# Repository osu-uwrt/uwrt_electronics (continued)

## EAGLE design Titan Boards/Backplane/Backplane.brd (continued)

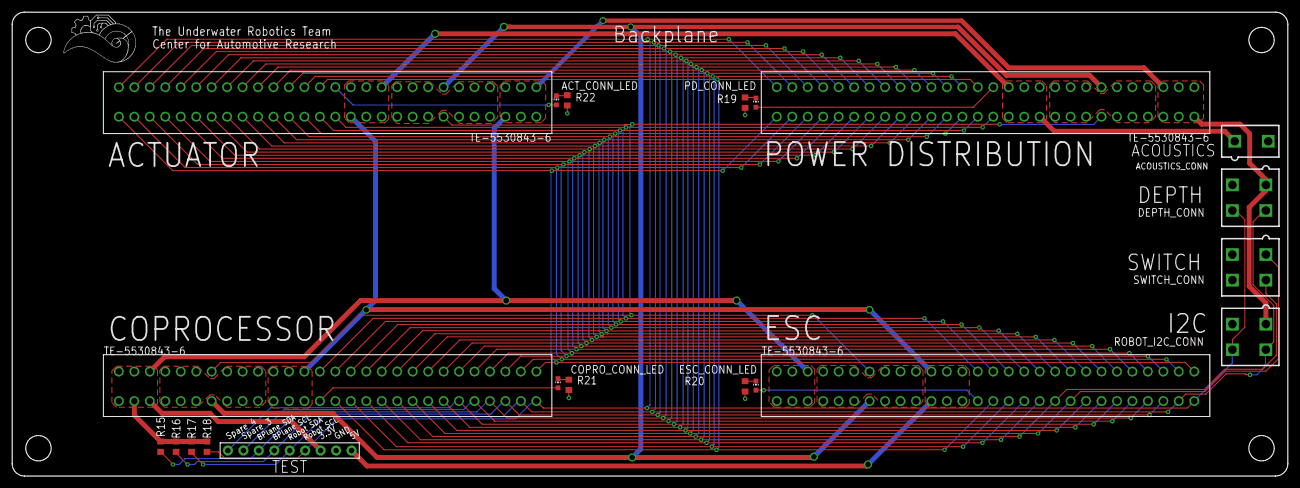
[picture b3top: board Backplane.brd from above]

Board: 2 copper layers, 209.6 x 76.2 mm, 21 parts (0 on the bottom side), 42 nets.

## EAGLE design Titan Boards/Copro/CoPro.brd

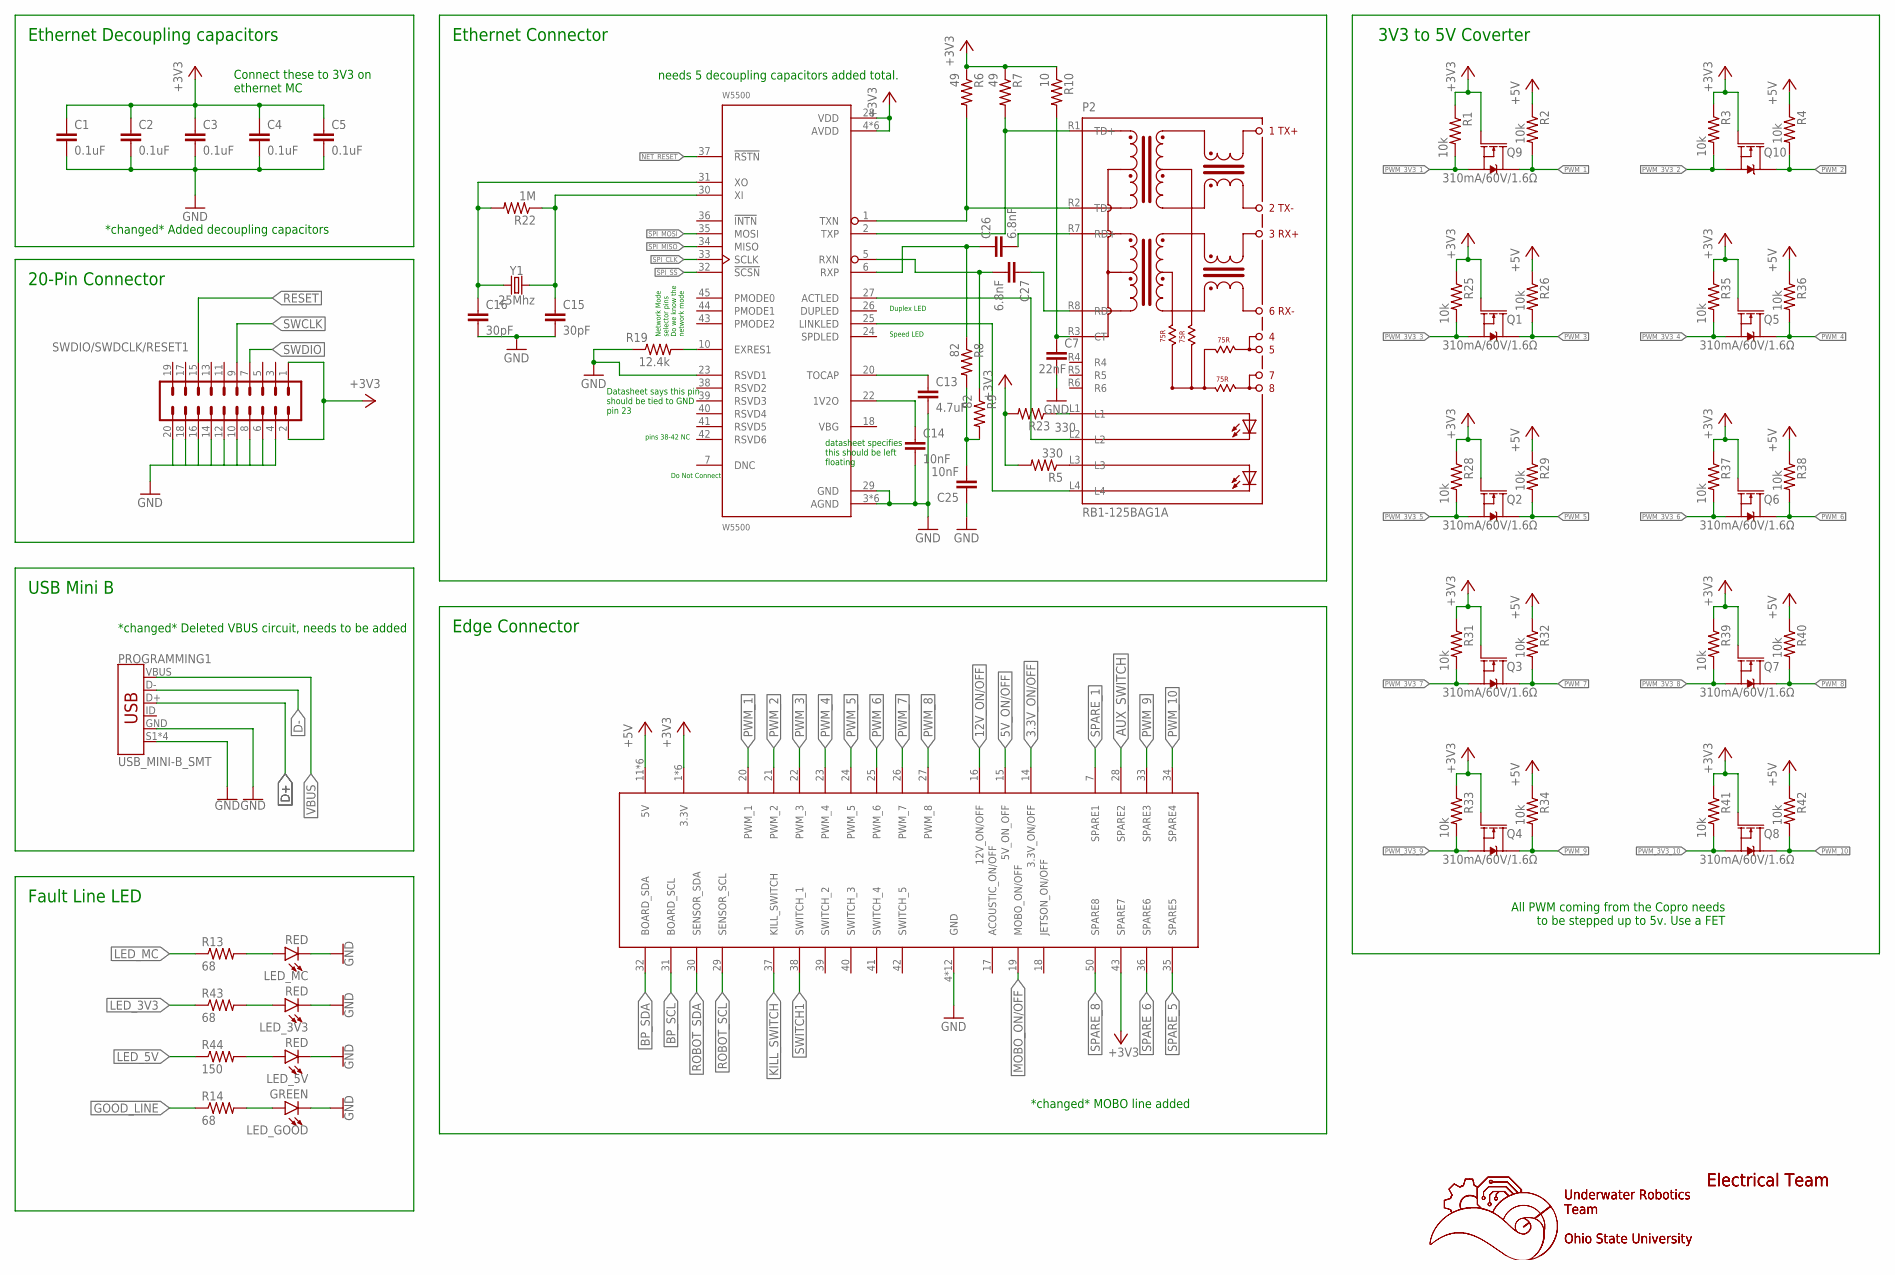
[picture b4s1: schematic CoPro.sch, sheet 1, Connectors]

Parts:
C1, C2, C3, C4, C5: 0.1uF; C0603
C7: 22nF; C0603
C13: 4.7uF; C0603
C14, C25: 10nF; C0603
C15, C16: 30pF; C0603
C26, C27: 6.8nF; C0603
LED_3V3, LED_5V: RED; LED-0603
LED_GOOD: GREEN; LED-0603
LED_MC: RED; LED-0603
P2: RB1-125BAG1A; WIZNET_RB1-125BAG1A
PROGRAMMING1: USB_MINI-B_SMT; USB-MINIB
Q1, Q2, Q3, Q4, Q5, Q6, Q7, Q8, Q9, Q10: 310mA/60V/1.6Ω; SOT323
R1, R2, R3, R4, R25, R26, R28, R29, R31, R32, R33, R34, R35, R36, R37, R38, R39, R40, R41, R42: 10k; R0603
R5, R23: 330; R0603
R6, R7: 49; R0603
R8, R9: 82; R0603
R10: 10; R0603
R13, R14, R43: 68; R0603
R19: 12.4k; R0603
R22: 1M; R0603
R44: 150; R0603
SWDIO/SWDCLK/RESET1: CONN_10X2; 2X10
U$1: 5530843-EDGE; 5530843-6-BOARDFINGERS
W5500: W5500; QFP50P900X900X160-48N
Y1: 25Mhz; HC49US

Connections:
3.3V_ON/OFF: U$1.14 (3.3V_ON/OFF); also elsewhere on the board
5V_ON/OFF: U$1.15 (5V_ON_OFF); also elsewhere on the board
12V_ON/OFF: U$1.16 (12V_ON/OFF); also elsewhere on the board
+3V3: C1.1, C2.1, C3.1, C4.1, C5.1, Q1.1 (G), Q2.1 (G), Q3.1 (G), Q4.1 (G), Q5.1 (G), Q6.1 (G), Q7.1 (G), Q8.1 (G), Q9.1 (G), Q10.1 (G), R1.1, R3.1, R5.2, R6.1, R7.1, R10.1, R23.2, R25.1, R28.1, R31.1, R33.1, R35.1, R37.1, R39.1, R41.1, SWDIO/SWDCLK/RESET1.1, SWDIO/SWDCLK/RESET1.2, U$1.1 (3.3V), U$1.2 (3.3V), U$1.3 (3.3V), U$1.43 (SPARE7), U$1.54 (3.3V), U$1.55 (3.3V), U$1.56 (3.3V), W5500.4 (AVDD), W5500.8 (AVDD), W5500.11 (AVDD), W5500.15 (AVDD), W5500.17 (AVDD), W5500.21 (AVDD), W5500.28 (VDD); also elsewhere on the board
+5V: R2.1, R4.1, R26.1, R29.1, R32.1, R34.1, R36.1, R38.1, R40.1, R42.1, U$1.11 (5V), U$1.12 (5V), U$1.13 (5V), U$1.44 (5V), U$1.45 (5V), U$1.46 (5V); also elsewhere on the board
AUX_SWITCH: U$1.28 (SPARE2)
BP_SCL: U$1.31 (BOARD_SCL); also elsewhere on the board
BP_SDA: U$1.32 (BOARD_SDA); also elsewhere on the board
D+: PROGRAMMING1.D+; also elsewhere on the board
D-: PROGRAMMING1.D-; also elsewhere on the board
GND: C1.2, C2.2, C3.2, C4.2, C5.2, C7.2, C13.2, C14.2, C15.2, C16.2, C25.1, LED_3V3.C, LED_5V.C, LED_GOOD.C, LED_MC.C, PROGRAMMING1.GND, PROGRAMMING1.S1 (SHIELD), PROGRAMMING1.S2 (SHIELD), PROGRAMMING1.S3 (SHIELD), PROGRAMMING1.S4 (SHIELD), R19.1, SWDIO/SWDCLK/RESET1.4, SWDIO/SWDCLK/RESET1.6, SWDIO/SWDCLK/RESET1.8, SWDIO/SWDCLK/RESET1.10, SWDIO/SWDCLK/RESET1.12, SWDIO/SWDCLK/RESET1.14, SWDIO/SWDCLK/RESET1.16, SWDIO/SWDCLK/RESET1.18, SWDIO/SWDCLK/RESET1.20, U$1.4 (GND), U$1.5 (GND), U$1.6 (GND), U$1.8 (GND), U$1.9 (GND), U$1.10 (GND), U$1.47 (GND), U$1.48 (GND), U$1.49 (GND), U$1.51 (GND), U$1.52 (GND), U$1.53 (GND), W5500.3 (AGND), W5500.9 (AGND), W5500.14 (AGND), W5500.16 (AGND), W5500.19 (AGND), W5500.23 (RSVD1), W5500.29 (GND), W5500.48 (AGND); also elsewhere on the board
GOOD_LINE: R14.1; also elsewhere on the board
KILL_SWITCH: U$1.37 (KILL_SWITCH); also elsewhere on the board
LED_3V3: R43.1; also elsewhere on the board
LED_5V: R44.1; also elsewhere on the board
LED_MC: R13.1; also elsewhere on the board
MOBO_ON/OFF: U$1.19 (MOBO_ON/OFF); also elsewhere on the board
unnamed: C14.1, W5500.22 (1V2O)
unnamed: LED_MC.A, R13.2
unnamed: C15.1, R22.1, W5500.30 (XI), Y1.2
unnamed: C16.1, R22.2, W5500.31 (XO), Y1.1
unnamed: P2.L4, W5500.25 (LINKLED)
unnamed: P2.L2, W5500.27 (ACTLED)
unnamed: C13.1, W5500.20 (TOCAP)
unnamed: R19.2, W5500.10 (EXRES1)
unnamed: P2.L1, R23.1
unnamed: P2.L3, R5.1
unnamed: C25.2, R8.2, R9.2
unnamed: P2.R1 (TD+), R7.2, W5500.2 (TXP)
unnamed: P2.R2 (TD-), R6.2, W5500.1 (TXN)
unnamed: C26.2, P2.R7 (RD+)
unnamed: C26.1, R8.1, W5500.6 (RXP)
unnamed: C27.2, R9.1, W5500.5 (RXN)
unnamed: C27.1, P2.R8 (RD-)
unnamed: C7.1, P2.R3 (CT), R10.2
unnamed: LED_3V3.A, R43.2
unnamed: LED_5V.A, R44.2
unnamed: LED_GOOD.A, R14.2
NET_RESET: W5500.37 (!RSTN); also elsewhere on the board
PWM_1: Q9.3 (D), R2.2, U$1.20 (PWM_1)
PWM_2: Q10.3 (D), R4.2, U$1.21 (PWM_2)
PWM_3: Q1.3 (D), R26.2, U$1.22 (PWM_3)
PWM_3V3_1: Q9.2 (S), R1.2; also elsewhere on the board
PWM_3V3_2: Q10.2 (S), R3.2; also elsewhere on the board
PWM_3V3_3: Q1.2 (S), R25.2; also elsewhere on the board
PWM_3V3_4: Q5.2 (S), R35.2; also elsewhere on the board
PWM_3V3_5: Q2.2 (S), R28.2; also elsewhere on the board
PWM_3V3_6: Q6.2 (S), R37.2; also elsewhere on the board
PWM_3V3_7: Q3.2 (S), R31.2; also elsewhere on the board
PWM_3V3_8: Q7.2 (S), R39.2; also elsewhere on the board
PWM_3V3_9: Q4.2 (S), R33.2; also elsewhere on the board
PWM_3V3_10: Q8.2 (S), R41.2; also elsewhere on the board
PWM_4: Q5.3 (D), R36.2, U$1.23 (PWM_4)
PWM_5: Q2.3 (D), R29.2, U$1.24 (PWM_5)
PWM_6: Q6.3 (D), R38.2, U$1.25 (PWM_6)
PWM_7: Q3.3 (D), R32.2, U$1.26 (PWM_7)
PWM_8: Q7.3 (D), R40.2, U$1.27 (PWM_8)
PWM_9: Q4.3 (D), R34.2, U$1.33 (SPARE3)
PWM_10: Q8.3 (D), R42.2, U$1.34 (SPARE4)
RESET: SWDIO/SWDCLK/RESET1.15; also elsewhere on the board
ROBOT_SCL: U$1.29 (SENSOR_SCL); also elsewhere on the board
ROBOT_SDA: U$1.30 (SENSOR_SDA); also elsewhere on the board
SPARE_1: U$1.7 (SPARE1); also elsewhere on the board
SPARE_5: U$1.35 (SPARE5); also elsewhere on the board
SPARE_6: U$1.36 (SPARE6); also elsewhere on the board
SPARE_8: U$1.50 (SPARE8); also elsewhere on the board
SPI_CLK: W5500.33 (SCLK); also elsewhere on the board
SPI_MISO: W5500.34 (MISO); also elsewhere on the board
SPI_MOSI: W5500.35 (MOSI); also elsewhere on the board
SPI_SS: W5500.32 (!SCSN); also elsewhere on the board
SWCLK: SWDIO/SWDCLK/RESET1.9; also elsewhere on the board
SWDIO: SWDIO/SWDCLK/RESET1.7; also elsewhere on the board
SWITCH1: U$1.38 (SWITCH_1); also elsewhere on the board
VBUS: PROGRAMMING1.VBUS; also elsewhere on the board

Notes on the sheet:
Underwater Robotics Team Ohio State University
Electrical Team
All PWM coming from the Copro needs to be stepped up to 5v. Use a FET
3V3 to 5V Coverter
datasheet specifies this should be left floating
Datasheet says this pin should be tied to GND pin 23
pins 38-42 NC
Do Not Connect
Duplex LED
Speed LED
Network Mode selector pins Do we know the network mode
Ethernet Connector
Edge Connector
20-Pin Connector
Fault Line LED
USB Mini B
needs 5 decoupling capacitors added total.
Ethernet Decoupling capacitors
Connect these to 3V3 on ethernet MC
*changed* Deleted VBUS circuit, needs to be added
*changed* Added decoupling capacitors
*changed* MOBO line added

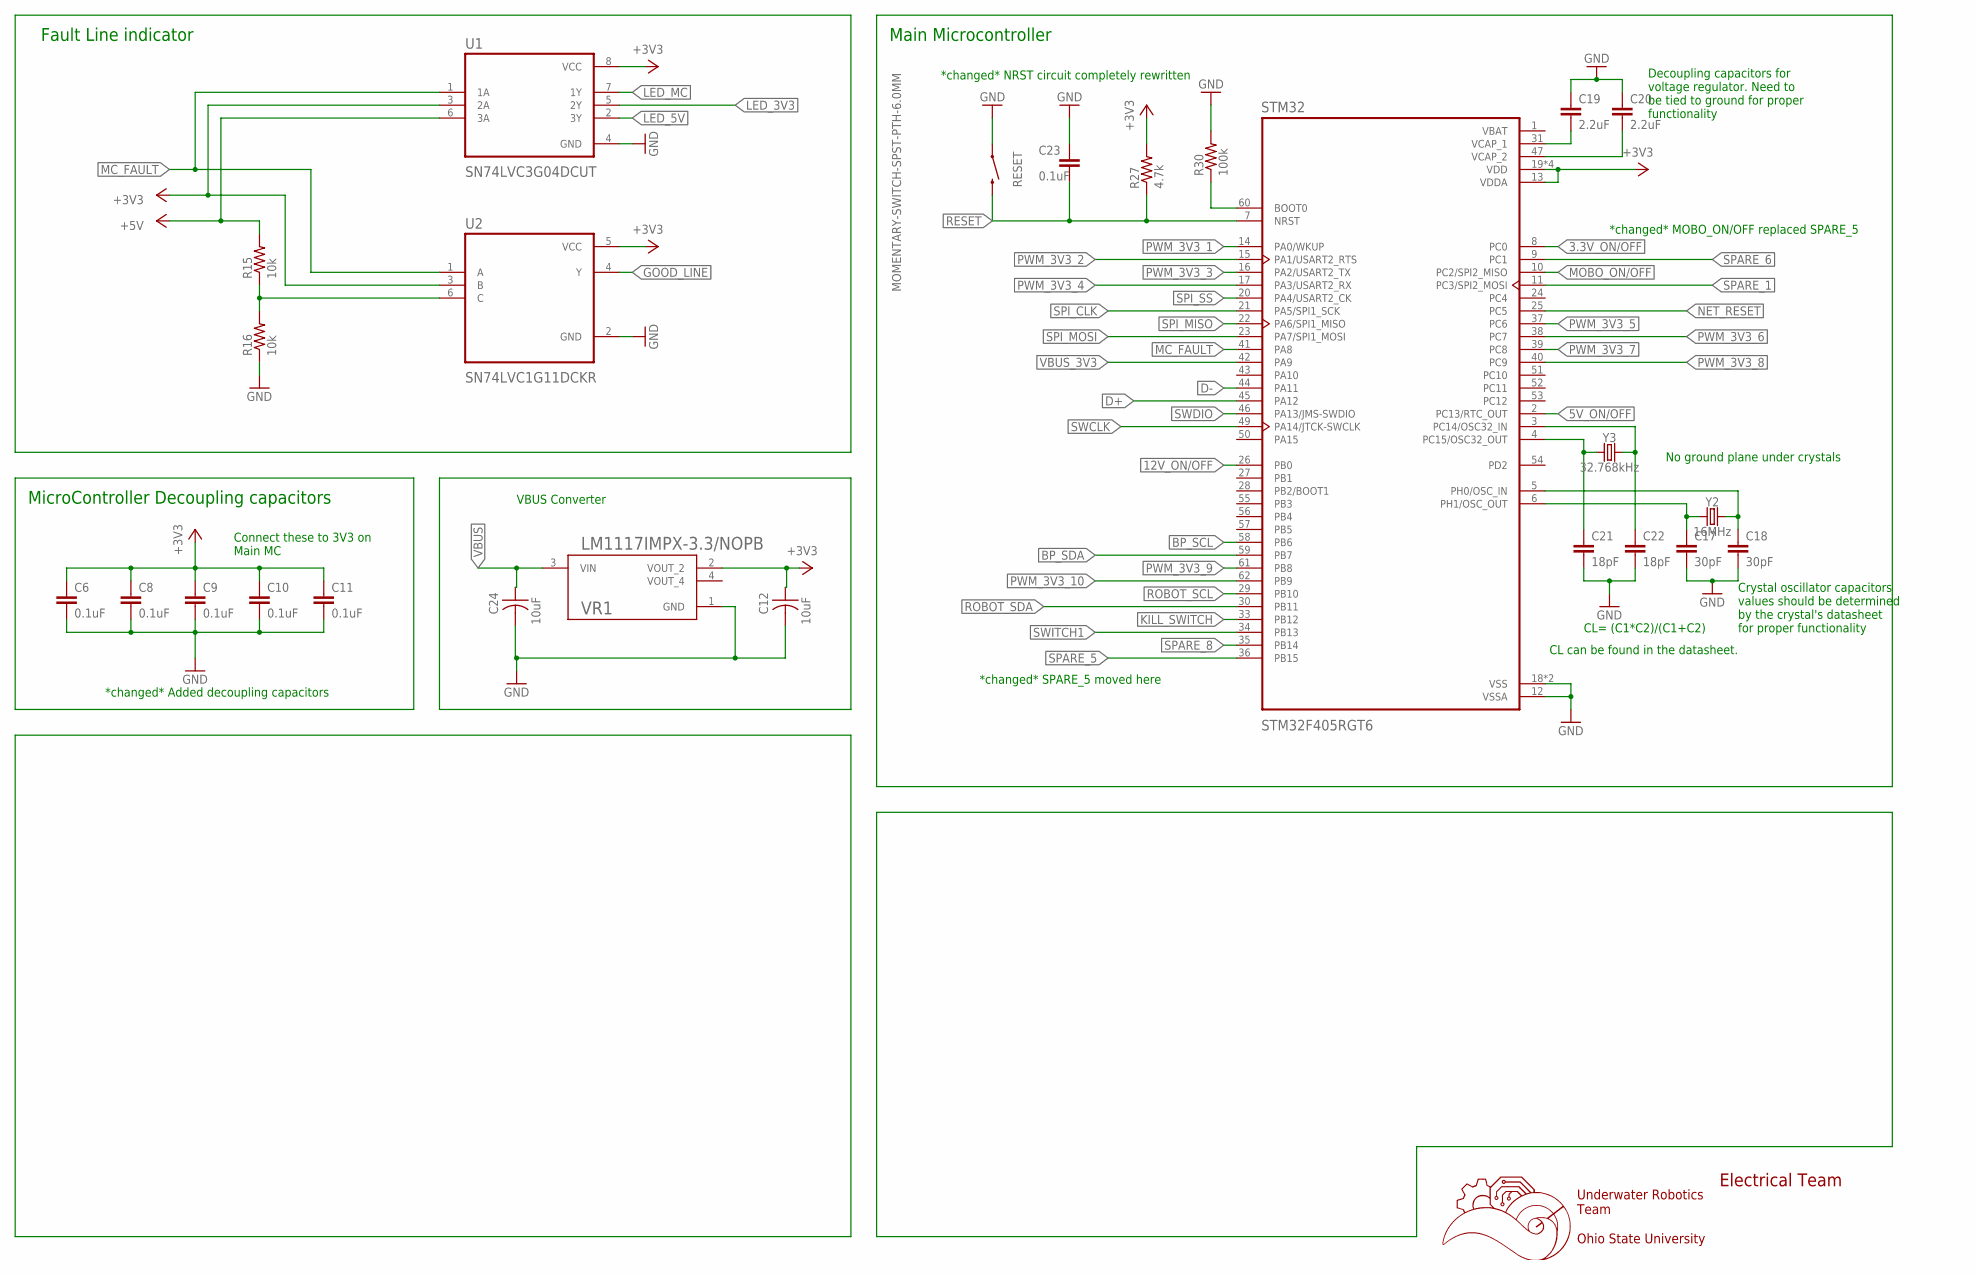
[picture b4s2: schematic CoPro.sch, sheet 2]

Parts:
C6, C8, C9, C10, C11, C23: 0.1uF; C0603
C12, C24: 10uF; C0603
C17, C18: 30pF; C0603
C19, C20: 2.2uF; C0603
C21, C22: 18pF; C0603
R15, R16: 10k; R0603
R27: 4.7k; R0603
R30: 100k; R0603
RESET: MOMENTARY-SWITCH-SPST-PTH-6.0MM; TACTILE_SWITCH_PTH_6.0MM
STM32: STM32F405RGT6; QFP50P1200X1200X160-64N
U1: SN74LVC3G04DCUT; SOP50P310X90-8N
U2: SN74LVC1G11DCKR; SOT65P210X110-6N
VR1: LM1117IMPX-3.3/NOPB; VREG_LM1117IMPX-3.3/NOPB
Y2: 16MHz; HC49US
Y3: 32.768kHz; CRYSTAL-SMD-3.2X1.5MM

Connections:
3.3V_ON/OFF: STM32.8 (PC0); also elsewhere on the board
5V_ON/OFF: STM32.2 (PC13/RTC_OUT); also elsewhere on the board
12V_ON/OFF: STM32.26 (PB0); also elsewhere on the board
+3V3: C6.1, C8.1, C9.1, C10.1, C11.1, C12.1, R27.2, STM32.13 (VDDA), STM32.19 (VDD), STM32.32 (VDD), STM32.48 (VDD), STM32.64 (VDD), U1.3 (2A), U1.8 (VCC), U2.3 (B), U2.5 (VCC), VR1.2 (VOUT_2); also elsewhere on the board
+5V: R15.2, U1.6 (3A); also elsewhere on the board
BP_SCL: STM32.58 (PB6); also elsewhere on the board
BP_SDA: STM32.59 (PB7); also elsewhere on the board
D+: STM32.45 (PA12); also elsewhere on the board
D-: STM32.44 (PA11); also elsewhere on the board
GND: C6.2, C8.2, C9.2, C10.2, C11.2, C12.2, C17.2, C18.2, C19.1, C20.1, C21.2, C22.2, C23.1, C24.2, R16.1, R30.2, RESET.1, STM32.12 (VSSA), STM32.18 (VSS), STM32.63 (VSS), U1.4 (GND), U2.2 (GND), VR1.1 (GND); also elsewhere on the board
GOOD_LINE: U2.4 (Y); also elsewhere on the board
KILL_SWITCH: STM32.33 (PB12); also elsewhere on the board
LED_3V3: U1.5 (2Y); also elsewhere on the board
LED_5V: U1.2 (3Y); also elsewhere on the board
LED_MC: U1.7 (1Y); also elsewhere on the board
MC_FAULT: STM32.41 (PA8), U1.1 (1A), U2.1 (A)
MOBO_ON/OFF: STM32.10 (PC2/SPI2_MISO); also elsewhere on the board
unnamed: C17.1, STM32.6 (PH1/OSC_OUT), Y2.1
unnamed: C18.1, STM32.5 (PH0/OSC_IN), Y2.2
unnamed: C20.2, STM32.47 (VCAP_2)
unnamed: C19.2, STM32.31 (VCAP_1)
unnamed: C21.1, STM32.4 (PC15/OSC32_OUT), Y3.P$1 (1)
unnamed: C22.1, STM32.3 (PC14/OSC32_IN), Y3.P$2 (2)
unnamed: R30.1, STM32.60 (BOOT0)
unnamed: R15.1, R16.2, U2.6 (C)
NET_RESET: STM32.25 (PC5); also elsewhere on the board
PWM_3V3_1: STM32.14 (PA0/WKUP); also elsewhere on the board
PWM_3V3_2: STM32.15 (PA1/USART2_RTS); also elsewhere on the board
PWM_3V3_3: STM32.16 (PA2/USART2_TX); also elsewhere on the board
PWM_3V3_4: STM32.17 (PA3/USART2_RX); also elsewhere on the board
PWM_3V3_5: STM32.37 (PC6); also elsewhere on the board
PWM_3V3_6: STM32.38 (PC7); also elsewhere on the board
PWM_3V3_7: STM32.39 (PC8); also elsewhere on the board
PWM_3V3_8: STM32.40 (PC9); also elsewhere on the board
PWM_3V3_9: STM32.61 (PB8); also elsewhere on the board
PWM_3V3_10: STM32.62 (PB9); also elsewhere on the board
RESET: C23.2, R27.1, RESET.3 (2), STM32.7 (NRST); also elsewhere on the board
ROBOT_SCL: STM32.29 (PB10); also elsewhere on the board
ROBOT_SDA: STM32.30 (PB11); also elsewhere on the board
SPARE_1: STM32.11 (PC3/SPI2_MOSI); also elsewhere on the board
SPARE_5: STM32.36 (PB15); also elsewhere on the board
SPARE_6: STM32.9 (PC1); also elsewhere on the board
SPARE_8: STM32.35 (PB14); also elsewhere on the board
SPI_CLK: STM32.21 (PA5/SPI1_SCK); also elsewhere on the board
SPI_MISO: STM32.22 (PA6/SPI1_MISO); also elsewhere on the board
SPI_MOSI: STM32.23 (PA7/SPI1_MOSI); also elsewhere on the board
SPI_SS: STM32.20 (PA4/USART2_CK); also elsewhere on the board
SWCLK: STM32.49 (PA14/JTCK-SWCLK); also elsewhere on the board
SWDIO: STM32.46 (PA13/JMS-SWDIO); also elsewhere on the board
SWITCH1: STM32.34 (PB13); also elsewhere on the board
VBAT: STM32.1 (VBAT)
VBUS: C24.1, VR1.3 (VIN); also elsewhere on the board
VBUS_3V3: STM32.42 (PA9)

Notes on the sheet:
Underwater Robotics Team Ohio State University
Electrical Team
Decoupling capacitors for voltage regulator. Need to be tied to ground for proper functionality
Crystal oscillator capacitors values should be determined by the crystal's datasheet for proper functionality
CL= (C1*C2)/(C1+C2)
CL can be found in the datasheet.
No ground plane under crystals
Main Microcontroller
Fault Line indicator
*changed* MOBO_ON/OFF replaced SPARE_5
*changed* SPARE_5 moved here
*changed* NRST circuit completely rewritten
MicroController Decoupling capacitors
Connect these to 3V3 on Main MC
*changed* Added decoupling capacitors
VBUS Converter

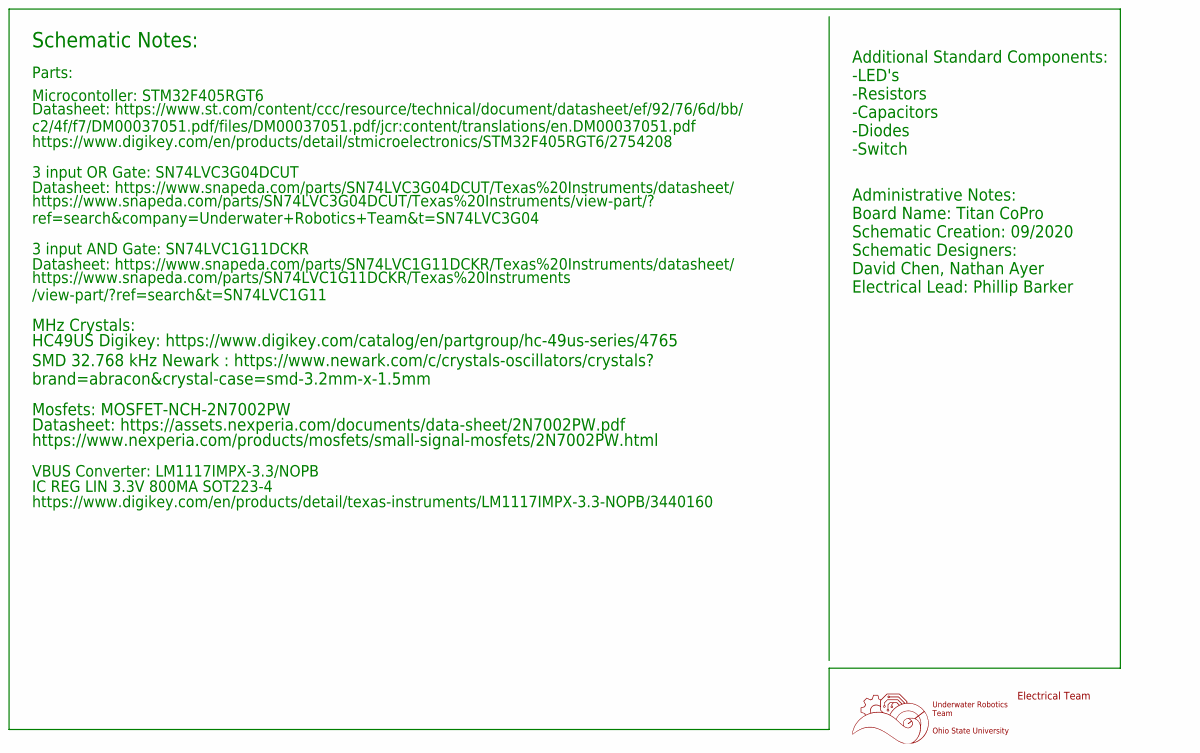
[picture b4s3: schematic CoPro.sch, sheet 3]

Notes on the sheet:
Underwater Robotics Team Ohio State University
Electrical Team
Schematic Notes:
Parts:
Microcontoller: STM32F405RGT6
Datasheet: https://www.st.com/content/ccc/resource/technical/document/datasheet/ef/92/76/6d/bb/ c2/4f/f7/DM00037051.pdf/files/DM00037051.pdf/jcr:content/translations/en.DM00037051.pdf
https://www.digikey.com/en/products/detail/stmicroelectronics/STM32F405RGT6/2754208
3 input OR Gate: SN74LVC3G04DCUT
Datasheet: https://www.snapeda.com/parts/SN74LVC3G04DCUT/Texas%20Instruments/datasheet/
https://www.snapeda.com/parts/SN74LVC3G04DCUT/Texas%20Instruments/view-part/? ref=search&company=Underwater+Robotics+Team&t=SN74LVC3G04
3 input AND Gate: SN74LVC1G11DCKR
Datasheet: https://www.snapeda.com/parts/SN74LVC1G11DCKR/Texas%20Instruments/datasheet/
https://www.snapeda.com/parts/SN74LVC1G11DCKR/Texas%20Instruments /view-part/?ref=search&t=SN74LVC1G11
Additional Standard Components: -LED's -Resistors -Capacitors -Diodes -Switch
Administrative Notes: Board Name: Titan CoPro Schematic Creation: 09/2020 Schematic Designers: David Chen, Nathan Ayer Electrical Lead: Phillip Barker
MHz Crystals:
HC49US Digikey: https://www.digikey.com/catalog/en/partgroup/hc-49us-series/4765
SMD 32.768 kHz Newark : https://www.newark.com/c/crystals-oscillators/crystals? brand=abracon&crystal-case=smd-3.2mm-x-1.5mm
Mosfets: MOSFET-NCH-2N7002PW
Datasheet: https://assets.nexperia.com/documents/data-sheet/2N7002PW.pdf
https://www.nexperia.com/products/mosfets/small-signal-mosfets/2N7002PW.html
VBUS Converter: LM1117IMPX-3.3/NOPB
IC REG LIN 3.3V 800MA SOT223-4
https://www.digikey.com/en/products/detail/texas-instruments/LM1117IMPX-3.3-NOPB/3440160

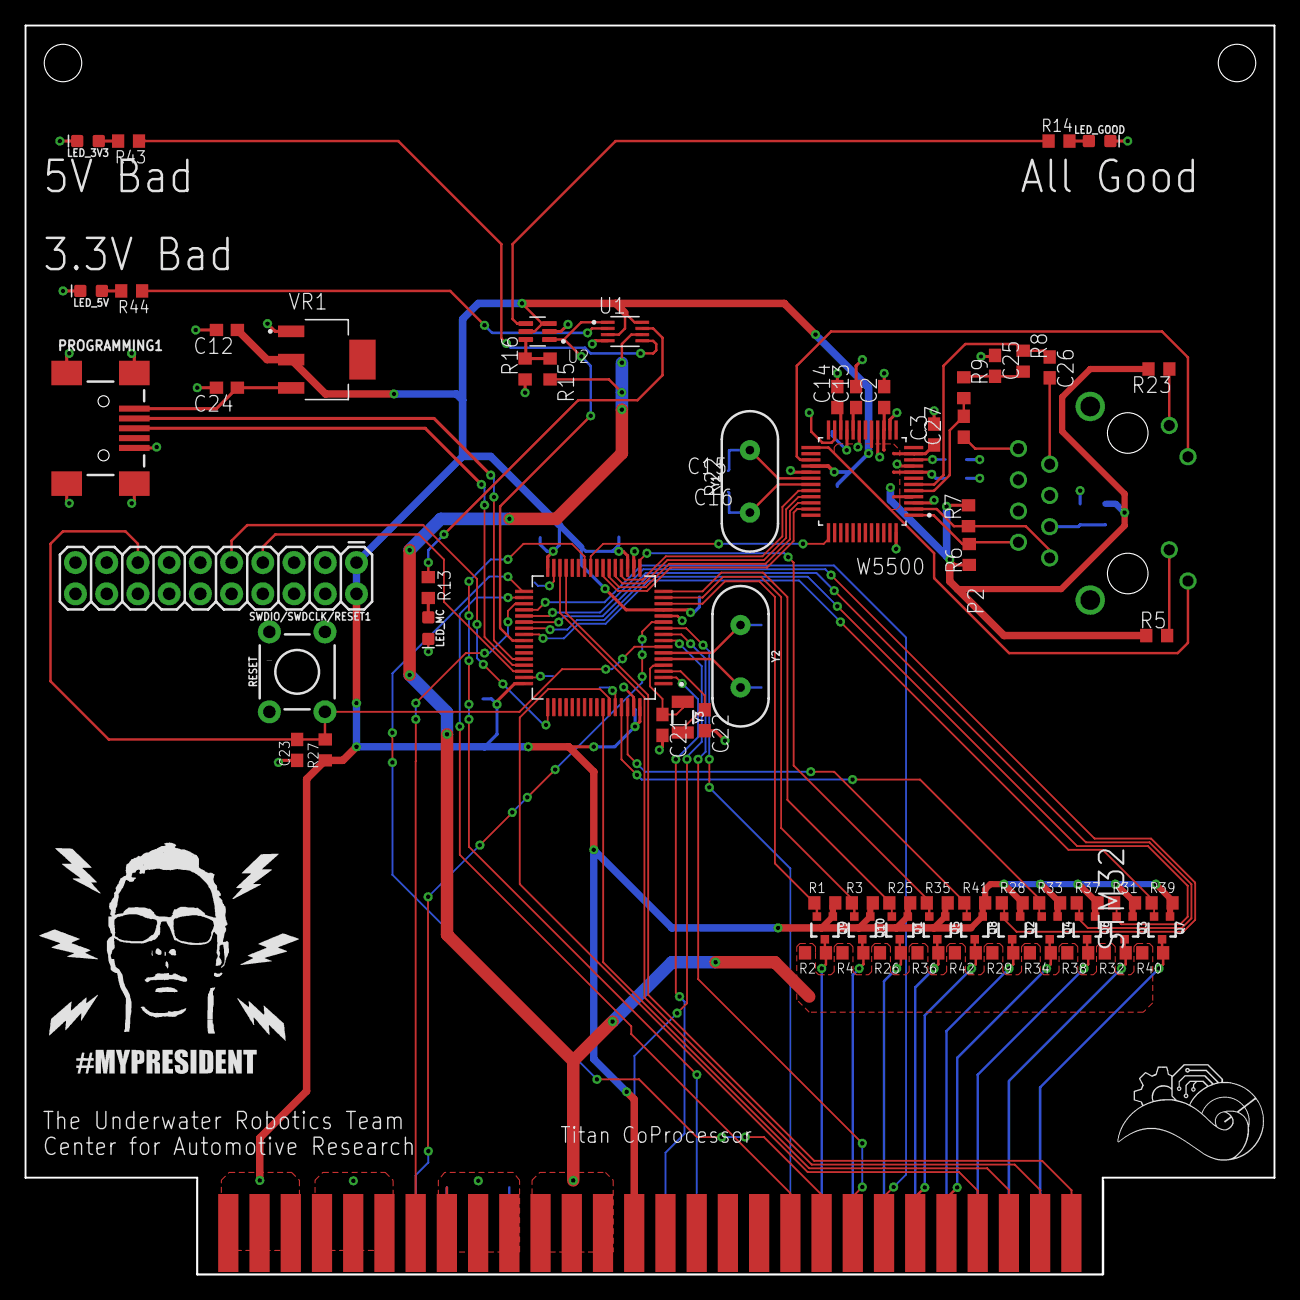
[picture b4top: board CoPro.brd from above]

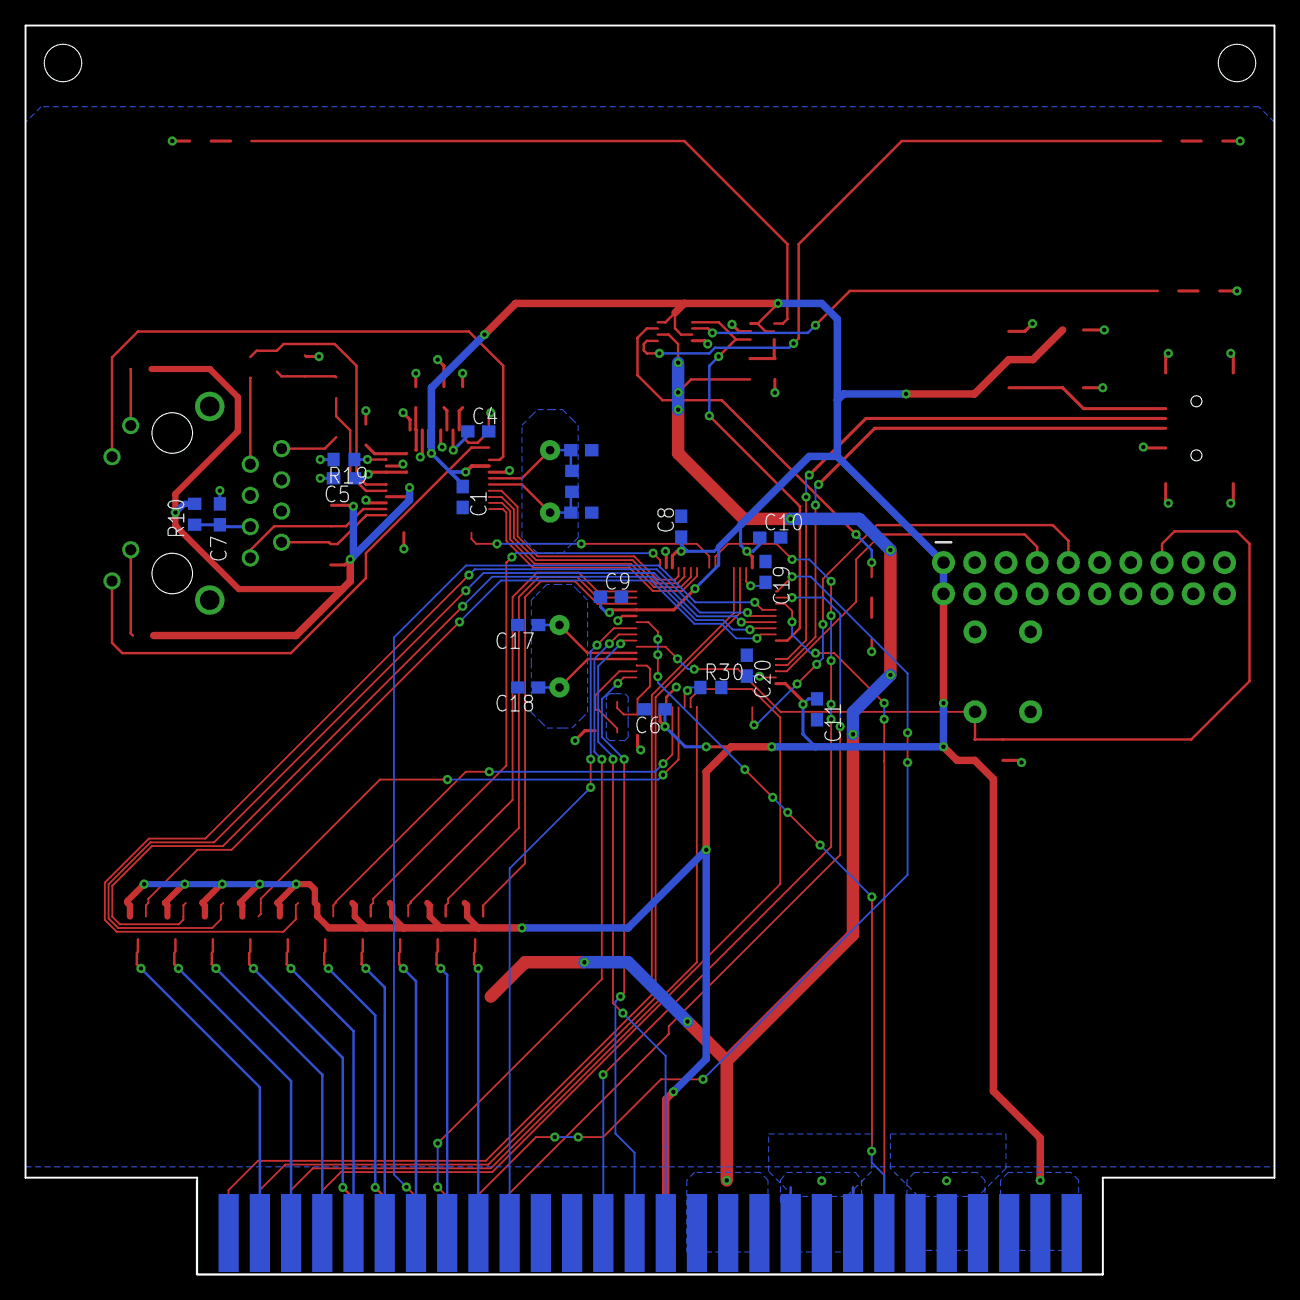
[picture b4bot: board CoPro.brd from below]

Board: 2 copper layers, 101.6 x 101.6 mm, 91 parts (19 on the bottom side), 82 nets.
